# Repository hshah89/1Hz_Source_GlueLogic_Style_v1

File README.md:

# 1Hz Clock Source: RTC Based

In this repo, I go over how to generate a 1Hz clock source through an unusual way.

Read full post write up here:

https://www.hackster.io/harit-shah/not-your-typical-1hz-source-5ee441

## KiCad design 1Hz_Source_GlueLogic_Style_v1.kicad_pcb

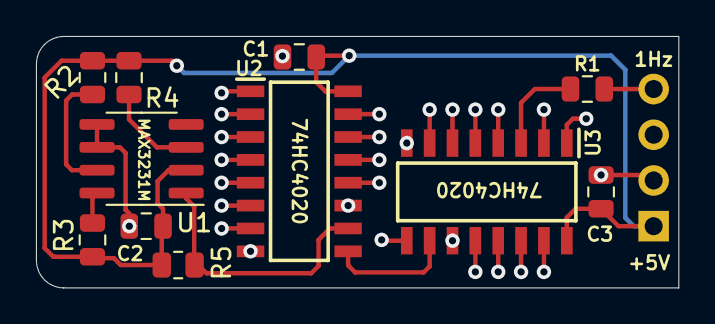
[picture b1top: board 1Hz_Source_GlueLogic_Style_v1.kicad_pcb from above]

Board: 2 copper layers, 35.7 x 14.0 mm, 12 parts (1 on the bottom side), 9 nets.

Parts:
C1, C2, C3: 1uF; C_0805_2012Metric
J1: Conn_01x04_Female; PinHeader_1x04_P2.54mm_Horizontal
R1: 0 ohm; R_0805_2012Metric
R2, R3, R4, R5: 4.7k; R_0805_2012Metric
U1: DS3232M; SOIC-8_3.9x4.9mm_P1.27mm
U2, U3: SN74HC4020DR; SOIC127P600X175-16N

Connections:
1Hz_out: J1.4, R1.2
+5V: C1.1, C2.1, C3.1, J1.1, R2.1, R3.1, R4.1, R5.1, U1.2, U2.16, U3.16
/32.768khz: R5.2, U1.1, U2.10
/clk_div_2: U2.9, U3.10
GND: C1.2, C2.2, C3.2, J1.2, J1.3, U1.5, U1.6, U2.8, U2.11, U3.8, U3.11
unnamed: R1.1, U3.3
unnamed: R2.2, U1.7
unnamed: R3.2, U1.8
unnamed: R4.2, U1.3

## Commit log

2021-02-01 post update
